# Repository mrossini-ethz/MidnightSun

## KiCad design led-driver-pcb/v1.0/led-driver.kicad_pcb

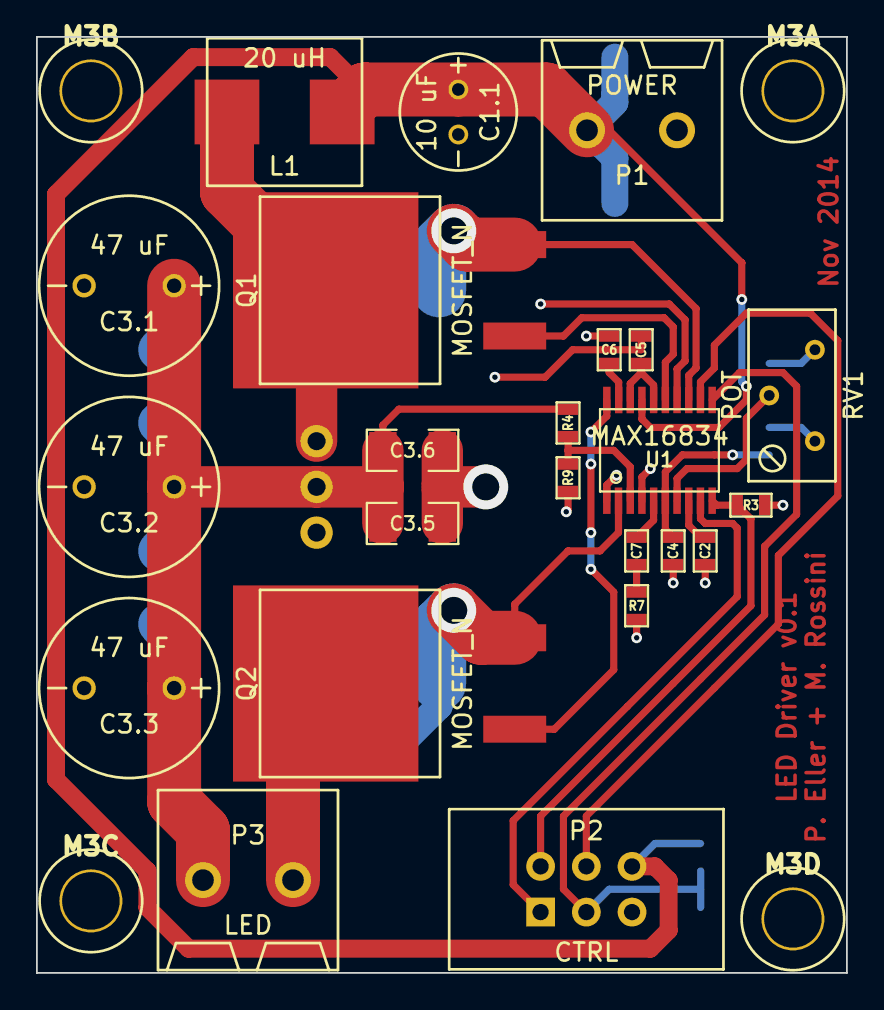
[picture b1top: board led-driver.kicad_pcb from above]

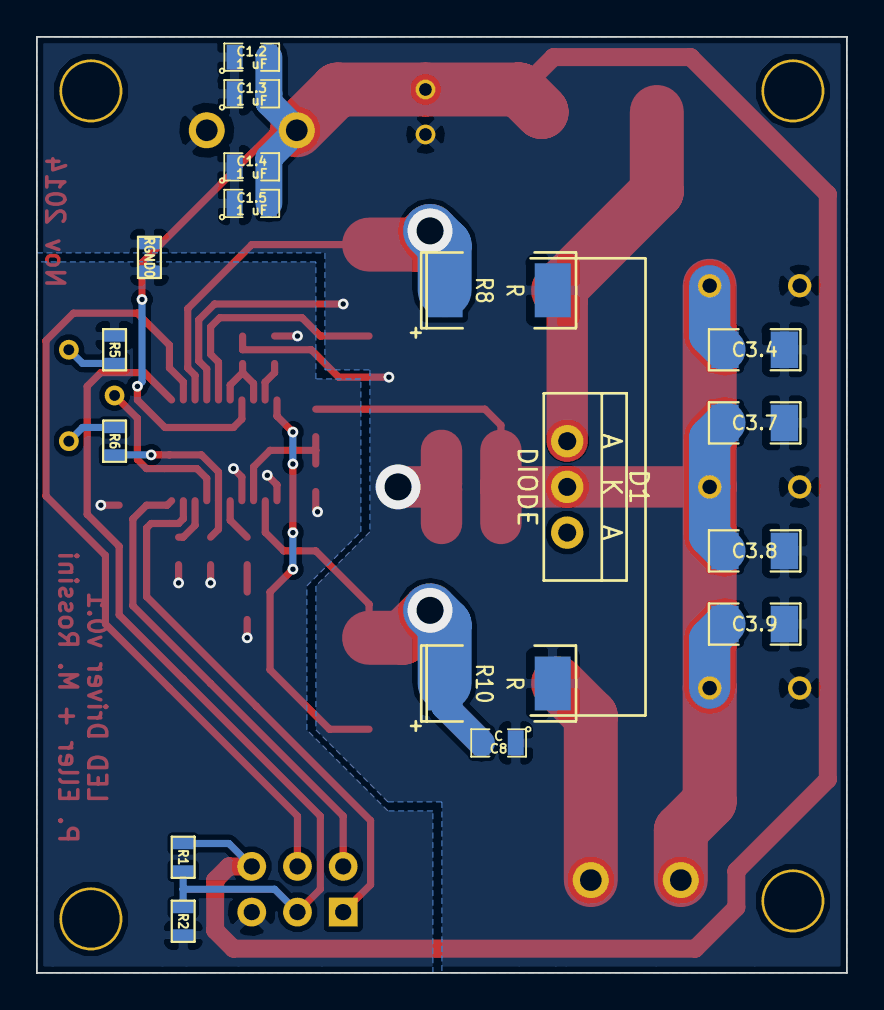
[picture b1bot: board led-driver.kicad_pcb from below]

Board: 2 copper layers, 45.0 x 52.0 mm, 44 parts (17 on the bottom side), 24 nets.

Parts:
C1.1: 10 uF; CP6.5x2.5
C1.2, C1.3, C1.4, C1.5: 1 uF; SM0805
C2, C4, C5, C6, C7: C; SM0603
C3.1, C3.2, C3.3: 47 uF; CP10x5
C3.4, C3.5, C3.6, C3.7, C3.8, C3.9: 1 uF; SM1206
C8: C; SM0805
D1: DIODE; TO220AB-Schottky
L1: 20 uH; LSMD8x8
M3A, M3B, M3C, M3D: P***; 1pin
P1: POWER; WAGO2P
P2: CTRL; PinHeader3x2
P3: LED; WAGO2P
Q1, Q2: MOSFET_N; D2PAK
R1, R2, R3, R4, R5, R6, R7, R9: R; SM0603
R8, R10: R; SM2512
RGND0: 0; SM0603
RV1: POT; RV_BOURNS
U1: MAX16834; tssop-20

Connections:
GND: C2.1, C4.1, C6.2, P2.5, R2.2, R3.2, R5.2, R7.2, R9.2, RGND0.2, U1.1, U1.4
GNDPWR: C1.1.2, C1.2.1, C1.3.1, C1.4.1, C1.5.1, C3.1.2, C3.2.2, C3.3.2, C3.4.1, C3.5.1, C3.6.1, C3.7.1, C3.8.1, C3.9.1, C5.2, C8.1, P1.1, R8.2, R10.2, RGND0.1, U1.14
unnamed: P2.4, U1.12
unnamed: R5.1, RV1.3
unnamed: C4.2, R6.1, U1.6
unnamed: P2.1, U1.9
unnamed: P2.2, R3.1, U1.10
unnamed: C2.2, U1.8
unnamed: RV1.2, U1.7
unnamed: R6.2, RV1.1
unnamed: P3.2, Q2.D
unnamed: P2.3, R1.2, R2.1, U1.11
unnamed: Q1.G, U1.15
unnamed: Q1.S, R8.1, U1.13
unnamed: Q2.G, U1.20
unnamed: R4.2, R9.1, U1.3
unnamed: C7.2, U1.5
unnamed: C7.1, R7.1
unnamed: C6.1, U1.19
unnamed: D1.1, L1.2, Q1.D
unnamed: C8.2, Q2.S, R10.1, U1.2
unnamed: C1.1.1, C1.2.2, C1.3.2, C1.4.2, C1.5.2, L1.1, P1.2, P2.6, R1.1, U1.17
unnamed: C5.1, U1.16, U1.18
unnamed: C3.1.1, C3.2.1, C3.3.1, C3.4.2, C3.5.2, C3.6.2, C3.7.2, C3.8.2, C3.9.2, D1.2, P3.1, R4.1

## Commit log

2014-10-21 Added the current version of the boost converter simulation and a script to calculate the device values for it.
2014-10-21 adding datasheets directory and pdfs for the first components
2014-10-21 Edited simulation and parameter script to match the 24 V power supply specs.
2014-10-21 added gitignore
2014-10-21 Added a KiCAD project and the schematic for the LED driver.
2014-10-21 Removed parameters for SUBCKT in Spice file so it will run on Mac.
2014-10-21 little plotter
2014-10-22 updated values in schema
2014-10-22 adding C2
2014-10-22 updated parts sepcs; added components.txt
2014-10-23 adding invoices dir and Mouser invoice
2014-10-31 Addeded more components to the purchasing list.
2014-10-31 Calculated the ID in the params file for component selection.
2014-10-31 Added the MOSFET component datasheet.
2014-10-31 Added footprints to the PCB of the LED driver and set up the PCB design.
2014-11-02 arranged components on PCB
2014-11-02 updated components on PCB
2014-11-02 Added a 3x2 pin header to the footprint library.
2014-11-02 Added power ratings for resistors in parameter calculater.
2014-11-03 Added components list for LED driver PCB.
2014-11-03 updated layout, added screwholes
2014-11-03 Finished the PCB design.
2014-11-03 Modified the gitignore file.
2014-11-04 Improved the params file for the LED driver by rounding values and adding more component values.
2014-11-04 Added the potentiometer datasheet.
2014-11-04 added pwrgnd layer
2014-11-04 Optimized design and put capacitor C1.1 also to power ground.
2014-11-04 Made more optimizations.
2014-11-04 Enhanced the LED driver parameter script to show temperatures of components.
2014-11-04 payments
2014-11-04 Added calculation of capacitor ripple currents and added some component suggestions.
2014-11-05 Exchanged capacitors and added new ones to allow for current ripple and to minimize ESR.
2014-11-05 Corrected the footprint of the MOSFETs.
2014-11-05 Edited .gitignore.
2014-11-07 Moved two ceramic capacitors closer to the diode.
2014-11-08 Added payment info.
2014-12-03 added firmware project; first version of PWM
2014-12-15 Added an intensity lookup table to smoothly control the LED intensity.
2014-12-16 Firmware: Changed PWM mode to phase correct such that 0 % and 100 % duty cycle are possible.
2014-12-16 Increased the MCU frequency to 2 MHz to enable 1 us pulses for dimming.
2015-02-16 Added a macros.h header file to simplify the setting of flags in registers and the handling of GPIO pins. Converted project to the Arduino Uno/Leonardo at the same time.
2015-02-17 Added a USART interface that at the moment just echos the input. Had to fix the system clock prescaling that was previously broken while doing so.
2015-02-21 Changed the PWM control from fixed frequency to variable frequency below a certain threshold intensity. This enhances resolution at the low end.
2015-05-17 Added a dim curve mechanism.
2015-05-18 arduino leonardo lufa
2015-05-21 Added the Arduino Boards to the payment list.
2015-05-21 Added wishlist for LED driver v2
2015-05-21 Updated driver wishlist
